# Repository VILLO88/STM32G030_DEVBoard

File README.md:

# STM32G030 Development Board

A compact STM32G030C8T6 development board designed for fast prototyping with breadboard-compatible pinout.

## Features

- **MCU:** STM32G030C8T6 (ARM Cortex-M0+, 64KB Flash, 8KB RAM)
- **Voltage Regulator:** AP2210N-3.3V (low dropout, 300mA)
- **USB Interface:** Micro-USB with CH340E USB-to-Serial converter
- **Oscillators:**
  - 8MHz external resonator (HSE)
  - 32.768kHz crystal (LSE for RTC)
- **User LED:** Connected to PC6
- **Status LEDs:** Power, TX, RX
- **Buttons:** Reset, Wake-up
- **Boot Jumper:** For entering bootloader mode
- **Debug:** STDC14 connector compatible with ST-Link
- **Power Input:** USB or external via screw terminal (VIN)
- **GPIO:** 2x20 pin headers (2.54mm pitch) - breadboard friendly

## Pinout

### Side A (J4)
| Pin | Function |
|-----|----------|
| A0-A7 | GPIO Port A |
| B0-B2 | GPIO Port B |
| B10-B12 | GPIO Port B |
| A8 | GPIO Port A |
| B15 | GPIO Port B |
| C7 | GPIO Port C |
| VIN | External Power Input |
| GND | Ground |
| 3V | 3.3V Output |

### Side B (J5)
| Pin | Function |
|-----|----------|
| A11-A12 | GPIO Port A |
| A15 | GPIO Port A |
| D0-D3 | GPIO Port D |
| C1-C4 | GPIO Port C |
| B3-B9 | GPIO Port B |
| C13 | GPIO Port C |
| BAT | Battery Input |
| RST | Reset |
| 3V | 3.3V Output |
| GND | Ground |

## Programming

### Using ST-Link (SWD)
Connect to the STDC14 header or the 4-pin PROG header:
- Pin 1: VCC (3.3V)
- Pin 2: GND
- Pin 3: SWDIO
- Pin 4: SWCLK

### Using USB Bootloader
1. Close the BOOT jumper (JP1)
2. Press Reset or power cycle the board
3. Use STM32CubeProgrammer to flash via USB

### Using CH340E Serial
The onboard CH340E provides USB-to-Serial conversion for:
- Serial debugging/communication
- Programming via UART bootloader

## Power Supply

The board can be powered via:
- **USB:** 5V from Micro-USB connector
- **VIN:** External supply (5-12V) via screw terminal (J1)
- **3V:** Direct 3.3V supply (bypasses regulator)

Protection diode (SS14) prevents reverse polarity damage.

## Bill of Materials

| Component | Value | Package | Quantity |
|-----------|-------|---------|----------|
| U2 | STM32G030C8Tx | LQFP-48 | 1 |
| U1 | AP2210N-3.3TRG1 | SOT-23-5 | 1 |
| U3 | CH340E | MSOP-10 | 1 |
| Y1 | 8MHz Resonator | SMD 3-pin | 1 |
| Y2 | 32.768kHz Crystal | ABS09 | 1 |
| D1 | Power LED | 0603 | 1 |
| D2 | User LED | 0603 | 1 |
| D3 | TX LED | 0603 | 1 |
| D4 | RX LED | 0603 | 1 |
| D5 | SS14 | SMA | 1 |
| J6 | USB Micro-B | Molex 105017 | 1 |

See `STM32G030_DEV/STM32G030_DEV.csv` for complete BOM.

## Board Images

### Top Side

### Bottom Side

## Design Files

- **Schematic & PCB:** KiCad 8 format in `STM32G030_DEV/`
- **Production Files:** Gerbers and assembly files in `STM32G030_DEV/production/`
- **Firmware:** STM32CubeIDE project in root directory

## Demo Firmware

The included STM32CubeIDE project is a test application that demonstrates UART communication by allowing the user to control the LED blink frequency via serial commands.

### Features
- User LED (PC6) blinks at a configurable frequency
- UART interface to change the blink frequency in real-time
- Uses the onboard CH340E USB-to-Serial converter

### Usage
1. Connect the board via USB
2. Open a serial terminal (115200 baud, 8N1)
3. Send commands to change the LED blink frequency

## Getting Started

1. Clone this repository
2. Open `PROGETTOCUBE.ioc` in STM32CubeMX to view/modify pin configuration
3. Open the project in STM32CubeIDE
4. Build and flash to the board

### Basic LED Control
The User LED is configured on PC6. Toggle it with:
```c
HAL_GPIO_TogglePin(USR_LED_GPIO_Port, USR_LED_Pin);
HAL_Delay(500);
```

## License

Open Hardware - See PCB silkscreen for details.

---
**Revision:** 0.1 (11/25)
**Design:** MV Lab

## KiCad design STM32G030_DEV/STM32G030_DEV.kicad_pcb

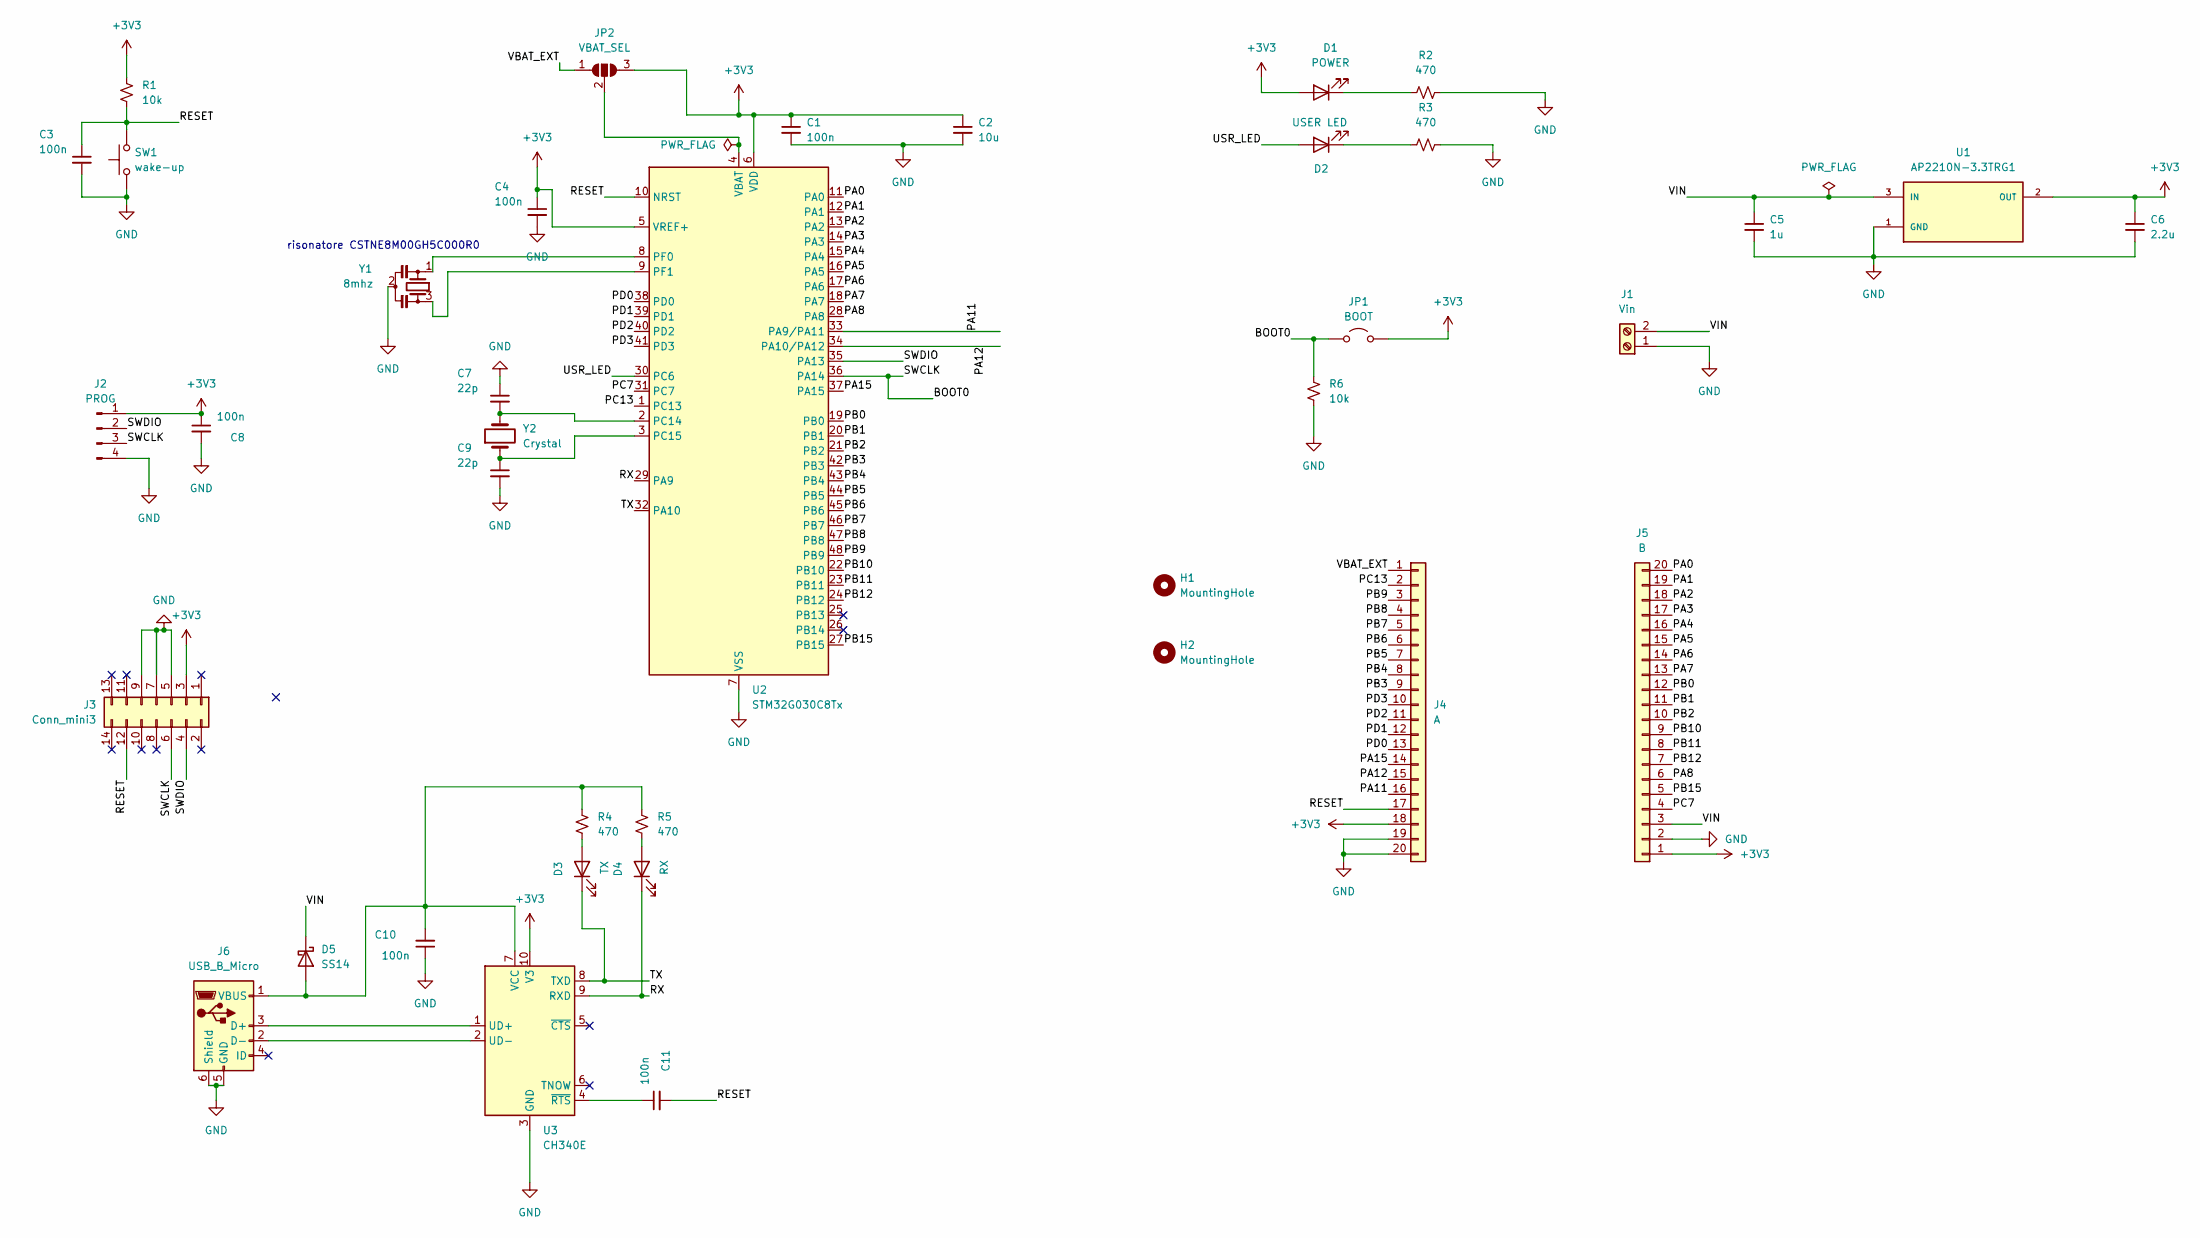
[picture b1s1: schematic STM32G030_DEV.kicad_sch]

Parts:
C1, C3, C4, C8, C10, C11: 100n; C_0603_1608Metric
C2: 10u; C_0603_1608Metric
C5: 1u; C_0603_1608Metric
C6: 2.2u; C_0603_1608Metric
C7, C9: 22p; C_0603_1608Metric
D1: POWER; LED_0603_1608Metric
D2: USER LED; LED_0603_1608Metric
D3: TX; LED_0603_1608Metric
D4: RX; LED_0603_1608Metric
D5: SS14; D_SMA
H1, H2: MountingHole; MountingHole_2.2mm_M2_ISO14580
J1: Vin; CUI_TB002-500-02BE
J2: PROG; PinHeader_1x04_P2.00mm_Vertical
J3: Conn_mini3; PinHeader_2x07_P1.27mm_Vertical
J4: A; PinHeader_1x20_P2.54mm_Vertical
J5: B; PinHeader_1x20_P2.54mm_Vertical
J6: USB_B_Micro; USB_Micro-B_Molex-105017-0001
JP1: BOOT; PinHeader_1x02_P2.54mm_Vertical
JP2: VBAT_SEL; SolderJumper-3_P1.3mm_Open_RoundedPad1.0x1.5mm_NumberLabels
R1, R6: 10k; R_0603_1608Metric
R2, R3, R4, R5: 470; R_0603_1608Metric
SW1: wake-up; SW_Tactile_SPST_NO_Straight_CK_PTS636Sx25SMTRLFS
U1: AP2210N-3.3TRG1; MPN AP2210N-3.3TRG1
U2: STM32G030C8Tx; LQFP-48_7x7mm_P0.5mm
U3: CH340E; MSOP-10_3x3mm_P0.5mm
Y1: 8mhz; Resonator_SMD_Murata_CSTxExxV-3Pin_3.0x1.1mm
Y2: Crystal; XTAL_ABS09-32.768KHZ-T

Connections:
+3V3: C1.1, C2.1, C4.1, C6.1, C8.1, D1.2 (A), J2.1, J3.3, J4.18, J5.1, JP1.2 (B), JP2.3 (B), R1.1, U1.2 (OUT), U2.5 (VREF+), U2.6 (VDD), U3.10 (V3)
/BOOT0: J2.3, J3.6, JP1.1 (A), R6.2, U2.36 (PA14)
/PA0: J5.20, U2.11 (PA0)
/PA1: J5.19, U2.12 (PA1)
/PA2: J5.18, U2.13 (PA2)
/PA3: J5.17, U2.14 (PA3)
/PA4: J5.16, U2.15 (PA4)
/PA5: J5.15, U2.16 (PA5)
/PA6: J5.14, U2.17 (PA6)
/PA7: J5.13, U2.18 (PA7)
/PA8: J5.6, U2.28 (PA8)
/PA11: J4.16, U2.33 (PA9/PA11)
/PA12: J4.15, U2.34 (PA10/PA12)
/PA15: J4.14, U2.37 (PA15)
/PB0: J5.12, U2.19 (PB0)
/PB1: J5.11, U2.20 (PB1)
/PB2: J5.10, U2.21 (PB2)
/PB3: J4.9, U2.42 (PB3)
/PB4: J4.8, U2.43 (PB4)
/PB5: J4.7, U2.44 (PB5)
/PB6: J4.6, U2.45 (PB6)
/PB7: J4.5, U2.46 (PB7)
/PB8: J4.4, U2.47 (PB8)
/PB9: J4.3, U2.48 (PB9)
/PB10: J5.9, U2.22 (PB10)
/PB11: J5.8, U2.23 (PB11)
/PB12: J5.7, U2.24 (PB12)
/PB15: J5.5, U2.27 (PB15)
/PC7: J5.4, U2.31 (PC7)
/PC13: J4.2, U2.1 (PC13)
/PD0: J4.13, U2.38 (PD0)
/PD1: J4.12, U2.39 (PD1)
/PD2: J4.11, U2.40 (PD2)
/PD3: J4.10, U2.41 (PD3)
/RESET: C3.1, C11.2, J3.12, J4.17, R1.2, SW1.2, U2.10 (NRST)
/RX: D4.1 (K), U2.29 (PA9), U3.9 (RXD)
/SWDIO: J2.2, J3.4, U2.35 (PA13)
/TX: D3.1 (K), U2.32 (PA10), U3.8 (TXD)
/USR_LED: D2.2 (A), U2.30 (PC6)
/VBAT_EXT: J4.1, JP2.1 (A)
/VIN: C5.1, D5.1 (K), J1.2, J5.3, U1.3 (IN)
GND: C1.2, C2.2, C3.2, C4.2, C5.2, C6.2, C7.1, C8.2, C9.2, C10.1, J1.1, J2.4, J3.5, J3.7, J3.9, J4.19, J4.20, J5.2, J6.5 (GND), J6.6 (Shield), R2.2, R3.2, R6.1, SW1.1, U1.1 (GND), U2.7 (VSS), U3.3 (GND), Y1.2
unnamed: D1.1 (K), R2.1
unnamed: D2.1 (K), R3.1
unnamed: D3.2 (A), R4.2
unnamed: D4.2 (A), R5.2
unnamed: C10.2, D5.2 (A), J6.1 (VBUS), R4.1, R5.1, U3.7 (VCC)
unnamed: J6.3 (D+), U3.1 (UD+)
unnamed: J6.2 (D-), U3.2 (UD-)
unnamed: JP2.2 (C), U2.4 (VBAT)
unnamed: C7.2, U2.2 (PC14), Y2.2
unnamed: C9.1, U2.3 (PC15), Y2.1
unnamed: U2.8 (PF0), Y1.1
unnamed: U2.9 (PF1), Y1.3
unnamed: C11.1, U3.4 (~RTS)

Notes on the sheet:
risonatore CSTNE8M00GH5C000R0

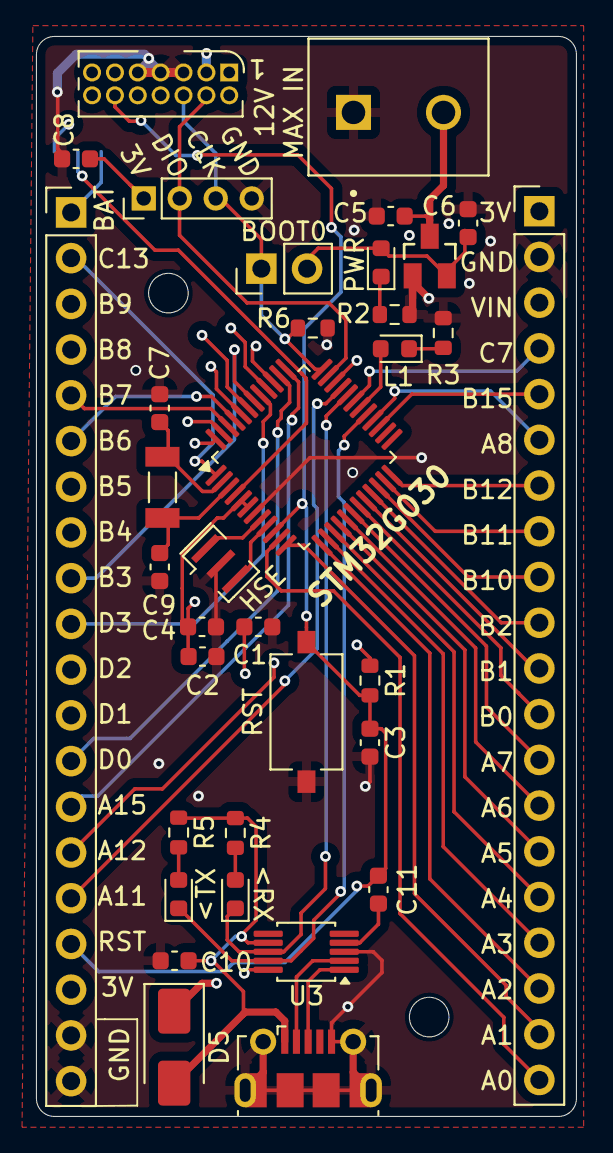
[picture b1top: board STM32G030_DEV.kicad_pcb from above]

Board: 4 copper layers, 30.0 x 60.0 mm, 38 parts (1 on the bottom side), 55 nets.

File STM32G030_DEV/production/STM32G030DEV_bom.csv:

Designator,Footprint,Quantity,Value,LCSC Part #
"C1, C10, C11, C3, C4, C8",0603,6,100n,
C2,0603,1,10u,
C5,0603,1,1u,
C6,0603,1,2.2u,
"C7, C9",0603,2,22p,
D1,0603,1,POWER,
D2,0603,1,USER LED,
D3,0603,1,TX,
D4,0603,1,RX,
D5,D_SMA,1,SS14,
J1,CUI_TB002-500-02BE,1,Vin,
J2,PinHeader_1x04_P2.00mm_Vertical,1,PROG,
J3,PinHeader_2x07_P1.27mm_Vertical,1,Conn_mini3,
J4,PinHeader_1x20_P2.54mm_Vertical,1,A,
J5,PinHeader_1x20_P2.54mm_Vertical,1,B,
J6,USB_Micro-B_Molex-105017-0001,1,USB_B_Micro,
JP1,PinHeader_1x02_P2.54mm_Vertical,1,BOOT,
"R1, R6",0603,2,10k,
"R2, R3, R4, R5",0603,4,470,
SW1,SW_Tactile_SPST_NO_Straight_CK_PTS636Sx25SMTRLFS,1,wake-up,
U1,AP2210N-3.3TRG1,1,AP2210N-3.3TRG1,AP2210N-3.3TRG1
U2,LQFP-48_7x7mm_P0.5mm,1,STM32G030C8Tx,
U3,MSOP-10_3x3mm_P0.5mm,1,CH340E,
Y1,Resonator_SMD_Murata_CSTxExxV-3Pin_3.0x1.1mm,1,8mhz,
Y2,XTAL_ABS09-32.768KHZ-T,1,Crystal,

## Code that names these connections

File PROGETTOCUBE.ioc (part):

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Mcu.Name=STM32G030C(6-8)Tx
Mcu.Package=LQFP48
Mcu.UserName=STM32G030C8Tx
PA10.Mode=Asynchronous
PA10.Signal=USART1_RX
PA13.Mode=Serial_Wire
PA13.Signal=SYS_SWDIO
PA14-BOOT0.Mode=Serial_Wire
PA14-BOOT0.Signal=SYS_SWCLK
PA9.Mode=Asynchronous
PA9.Signal=USART1_TX
PC14-OSC32_IN\ (PC14).Mode=LSE-External-Oscillator
PC14-OSC32_IN\ (PC14).Signal=RCC_OSC32_IN
PC15-OSC32_OUT\ (PC15).Mode=LSE-External-Oscillator
PC15-OSC32_OUT\ (PC15).Signal=RCC_OSC32_OUT
PC6.GPIOParameters=GPIO_Label
PC6.GPIO_Label=USR_LED
PC6.Signal=GPIO_Output
PF0-OSC_IN\ (PF0).Mode=HSE-External-Oscillator
PF0-OSC_IN\ (PF0).Signal=RCC_OSC_IN
PF1-OSC_OUT\ (PF1).Mode=HSE-External-Oscillator
PF1-OSC_OUT\ (PF1).Signal=RCC_OSC_OUT
RCC.HSE_VALUE=8000000
RCC.SYSCLKFreq_VALUE=16000000
board=custom

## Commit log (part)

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2026-02-17 Repo upload
2026-02-17 Add KiCad PCB design files
2026-02-17 Add detailed README with board documentation
2026-02-17 Add demo firmware description to README
